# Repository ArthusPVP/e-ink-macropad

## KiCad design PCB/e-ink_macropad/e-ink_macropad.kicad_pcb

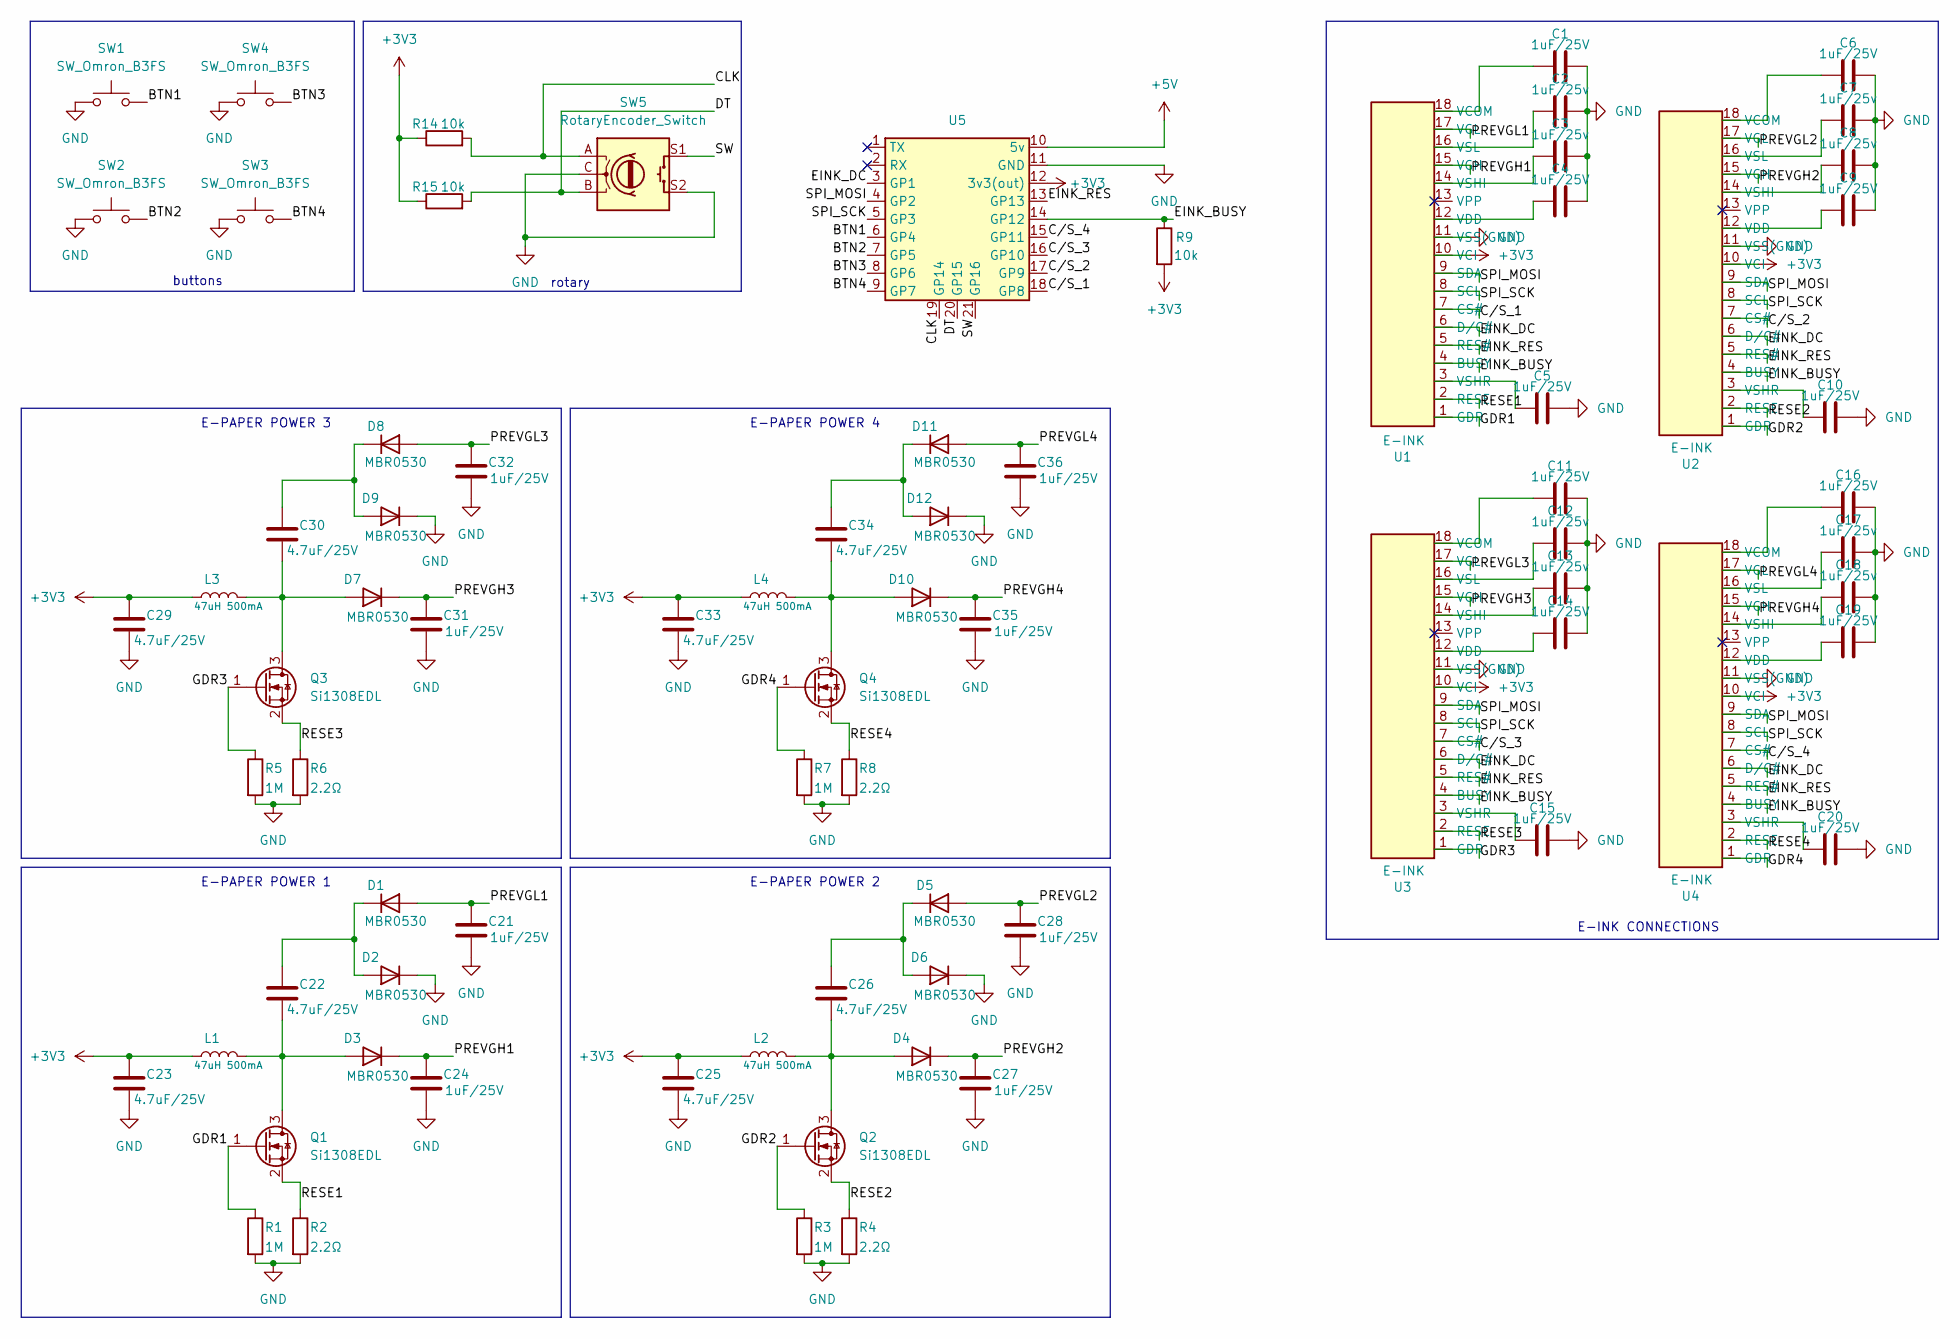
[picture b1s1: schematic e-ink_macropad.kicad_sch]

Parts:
C1, C4, C5, C6, C9, C10, C11, C14, C15, C16, C19, C20, C21, C24, C27, C28, C31, C32, C35, C36: 1uF/25V; C_01005_0402Metric
C2, C3, C7, C8, C12, C13, C17, C18: 1uF/25v; C_01005_0402Metric
C22, C23, C25, C26, C29, C30, C33, C34: 4.7uF/25V; C_01005_0402Metric
D1, D2, D3, D4, D5, D6, D7, D8, D9, D10, D11, D12: MBR0530; D_SOD-123
L1, L2, L3, L4: 47uH 500mA; L_1206_3216Metric
Q1, Q2, Q3, Q4: Si1308EDL; SOT-323_SC-70
R1, R3, R5, R7: 1M; R_0402_1005Metric
R2, R4, R6, R8: 2.2Ω; R_0402_1005Metric
R9, R14, R15: 10k; R_0402_1005Metric
SW1, SW2, SW3, SW4: SW_Omron_B3FS; SW__CHERRY
SW5: RotaryEncoder_Switch; RotaryEncoder_Alps_EC11E_Vertical_H20mm
U1, U2, U3, U4: E-INK; Amphenol_F32Q-1A7x1-11018_1x18-1MP_P0.5mm_Horizontal
U5: MODULE_ESP32-C3_SUPERMINI

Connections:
+3V3: C23.1, C25.1, C29.1, C33.1, L1.1, L2.1, L3.1, L4.1, R9.2, R14.1, R15.1, U1.10 (VCI), U2.10 (VCI), U3.10 (VCI), U4.10 (VCI), U5.12 (3v3(out))
+5V: U5.10 (5v)
/BTN1: SW1.2, U5.6 (GP4)
/BTN2: SW2.2, U5.7 (GP5)
/BTN3: SW4.2, U5.8 (GP6)
/BTN4: SW3.2, U5.9 (GP7)
/CLK: R14.2, SW5.A, U5.19 (GP14)
/C/S_1: U1.7 (CS#), U5.18 (GP8)
/C/S_2: U2.7 (CS#), U5.17 (GP9)
/C/S_3: U3.7 (CS#), U5.16 (GP10)
/C/S_4: U4.7 (CS#), U5.15 (GP11)
/DT: R15.2, SW5.B, U5.20 (GP15)
/EINK_BUSY: R9.1, U1.4 (BUSY), U2.4 (BUSY), U3.4 (BUSY), U4.4 (BUSY), U5.14 (GP12)
/EINK_DC: U1.6 (D/C#), U2.6 (D/C#), U3.6 (D/C#), U4.6 (D/C#), U5.3 (GP1)
/EINK_RES: U1.5 (RES#), U2.5 (RES#), U3.5 (RES#), U4.5 (RES#), U5.13 (GP13)
/GDR1: Q1.1 (G), R1.1, U1.1 (GDR)
/GDR2: Q2.1 (G), R3.1, U2.1 (GDR)
/GDR3: Q3.1 (G), R5.1, U3.1 (GDR)
/GDR4: Q4.1 (G), R7.1, U4.1 (GDR)
/PREVGH1: C24.1, D3.1 (K), U1.15 (VGH)
/PREVGH2: C27.1, D4.1 (K), U2.15 (VGH)
/PREVGH3: C31.1, D7.1 (K), U3.15 (VGH)
/PREVGH4: C35.1, D10.1 (K), U4.15 (VGH)
/PREVGL1: C21.1, D1.2 (A), U1.17 (VGL)
/PREVGL2: C28.1, D5.2 (A), U2.17 (VGL)
/PREVGL3: C32.1, D8.2 (A), U3.17 (VGL)
/PREVGL4: C36.1, D11.2 (A), U4.17 (VGL)
/RESE1: Q1.2 (S), R2.1, U1.2 (RESE)
/RESE2: Q2.2 (S), R4.1, U2.2 (RESE)
/RESE3: Q3.2 (S), R6.1, U3.2 (RESE)
/RESE4: Q4.2 (S), R8.1, U4.2 (RESE)
/SPI_MOSI: U1.9 (SDA), U2.9 (SDA), U3.9 (SDA), U4.9 (SDA), U5.4 (GP2)
/SPI_SCK: U1.8 (SCL), U2.8 (SCL), U3.8 (SCL), U4.8 (SCL), U5.5 (GP3)
/SW: SW5.S1, U5.21 (GP16)
GND: C1.2, C2.2, C3.2, C4.2, C5.2, C6.2, C7.2, C8.2, C9.2, C10.2, C11.2, C12.2, C13.2, C14.2, C15.2, C16.2, C17.2, C18.2, C19.2, C20.2, C21.2, C23.2, C24.2, C25.2, C27.2, C28.2, C29.2, C31.2, C32.2, C33.2, C35.2, C36.2, D2.1 (K), D6.1 (K), D9.1 (K), D12.1 (K), R1.2, R2.2, R3.2, R4.2, R5.2, R6.2, R7.2, R8.2, SW1.1, SW2.1, SW3.1, SW4.1, SW5.C, SW5.MP, SW5.S2, U1.11 (VSS(GND)), U1.MP, U2.11 (VSS(GND)), U2.MP, U3.11 (VSS(GND)), U3.MP, U4.11 (VSS(GND)), U4.MP, U5.11 (GND)
unnamed: C22.1, D1.1 (K), D2.2 (A)
unnamed: C22.2, D3.2 (A), L1.2, Q1.3 (D)
unnamed: C26.2, D4.2 (A), L2.2, Q2.3 (D)
unnamed: C26.1, D5.1 (K), D6.2 (A)
unnamed: C30.2, D7.2 (A), L3.2, Q3.3 (D)
unnamed: C30.1, D8.1 (K), D9.2 (A)
unnamed: C34.2, D10.2 (A), L4.2, Q4.3 (D)
unnamed: C34.1, D11.1 (K), D12.2 (A)
unnamed: C1.1, U1.18 (VCOM)
unnamed: C4.1, U1.12 (VDD)
unnamed: C3.1, U1.14 (VSHI)
unnamed: C5.1, U1.3 (VSHR)
unnamed: C2.1, U1.16 (VSL)
unnamed: C6.1, U2.18 (VCOM)
unnamed: C9.1, U2.12 (VDD)
unnamed: C8.1, U2.14 (VSHI)
unnamed: C10.1, U2.3 (VSHR)
unnamed: C7.1, U2.16 (VSL)
unnamed: C11.1, U3.18 (VCOM)
unnamed: C14.1, U3.12 (VDD)
unnamed: C13.1, U3.14 (VSHI)
unnamed: C15.1, U3.3 (VSHR)
unnamed: C12.1, U3.16 (VSL)
unnamed: C16.1, U4.18 (VCOM)
unnamed: C19.1, U4.12 (VDD)
unnamed: C18.1, U4.14 (VSHI)
unnamed: C20.1, U4.3 (VSHR)
unnamed: C17.1, U4.16 (VSL)

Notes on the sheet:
E-PAPER POWER 2
E-INK CONNECTIONS
E-PAPER POWER 1
E-PAPER POWER 3
rotary
buttons
E-PAPER POWER 4

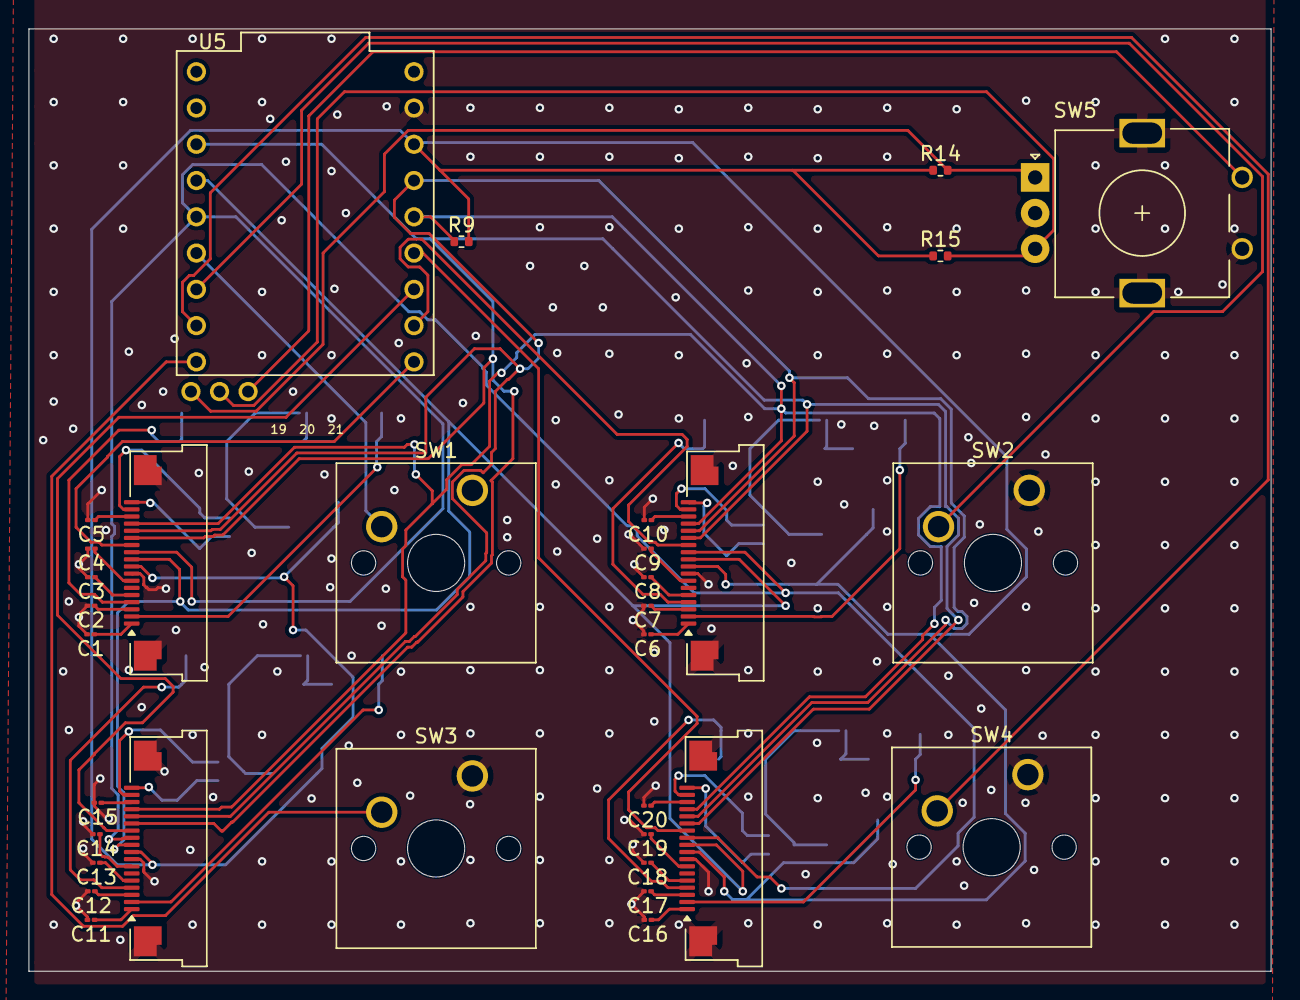
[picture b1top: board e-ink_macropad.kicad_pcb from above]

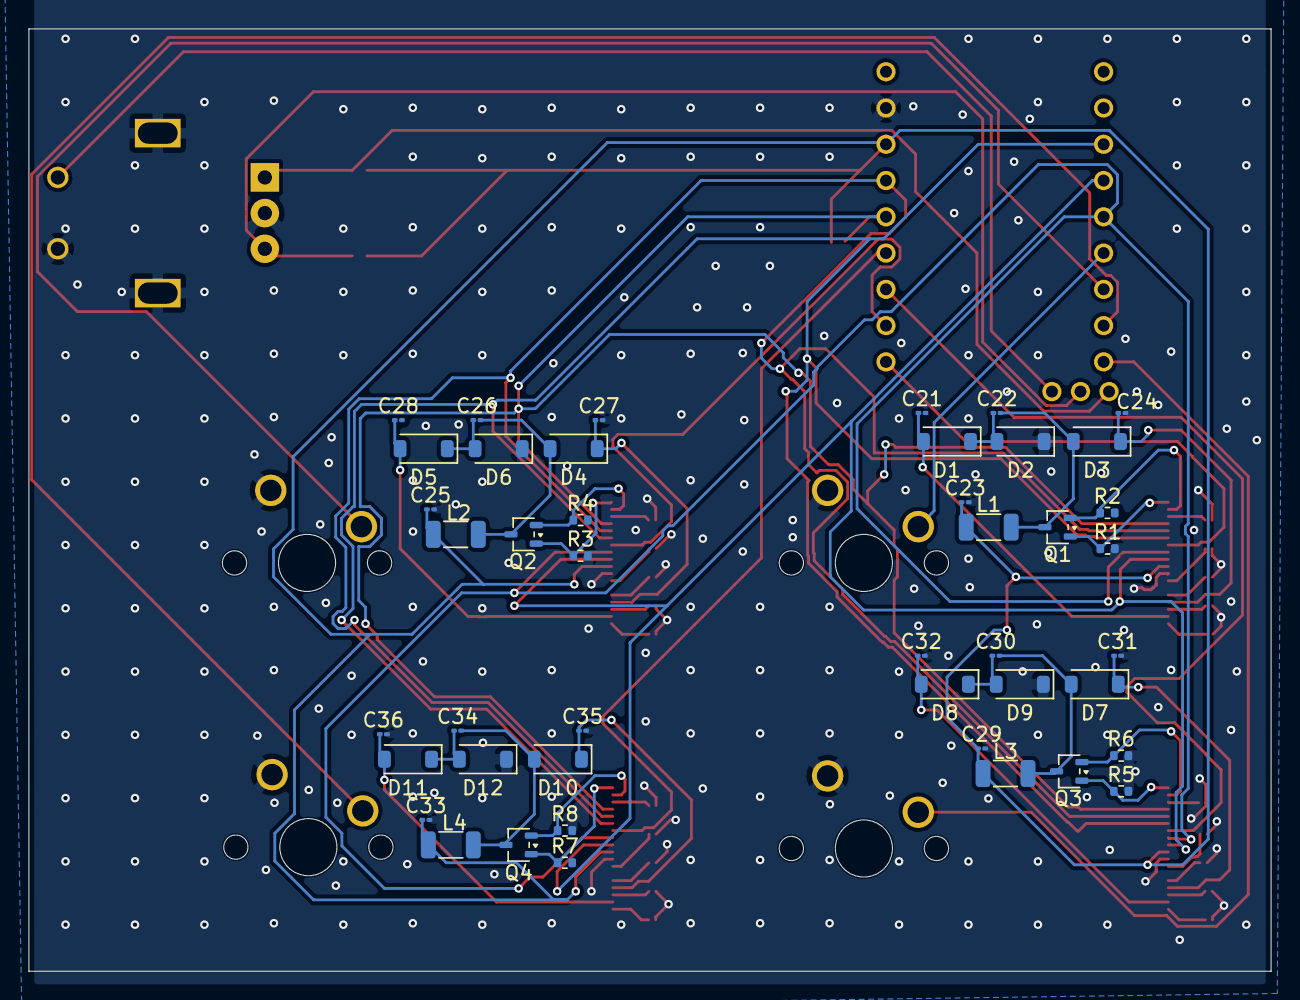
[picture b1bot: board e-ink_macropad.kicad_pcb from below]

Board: 2 copper layers, 87.0 x 66.0 mm, 77 parts (44 on the bottom side), 62 nets.

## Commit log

2026-06-06 Initiallised code for the repository
2026-06-06 updated into subfolder
2026-06-08 Finished the schematic and started the PCB Added files for kicad with the finished schematic
2026-06-08 Finalised the PCB layout
